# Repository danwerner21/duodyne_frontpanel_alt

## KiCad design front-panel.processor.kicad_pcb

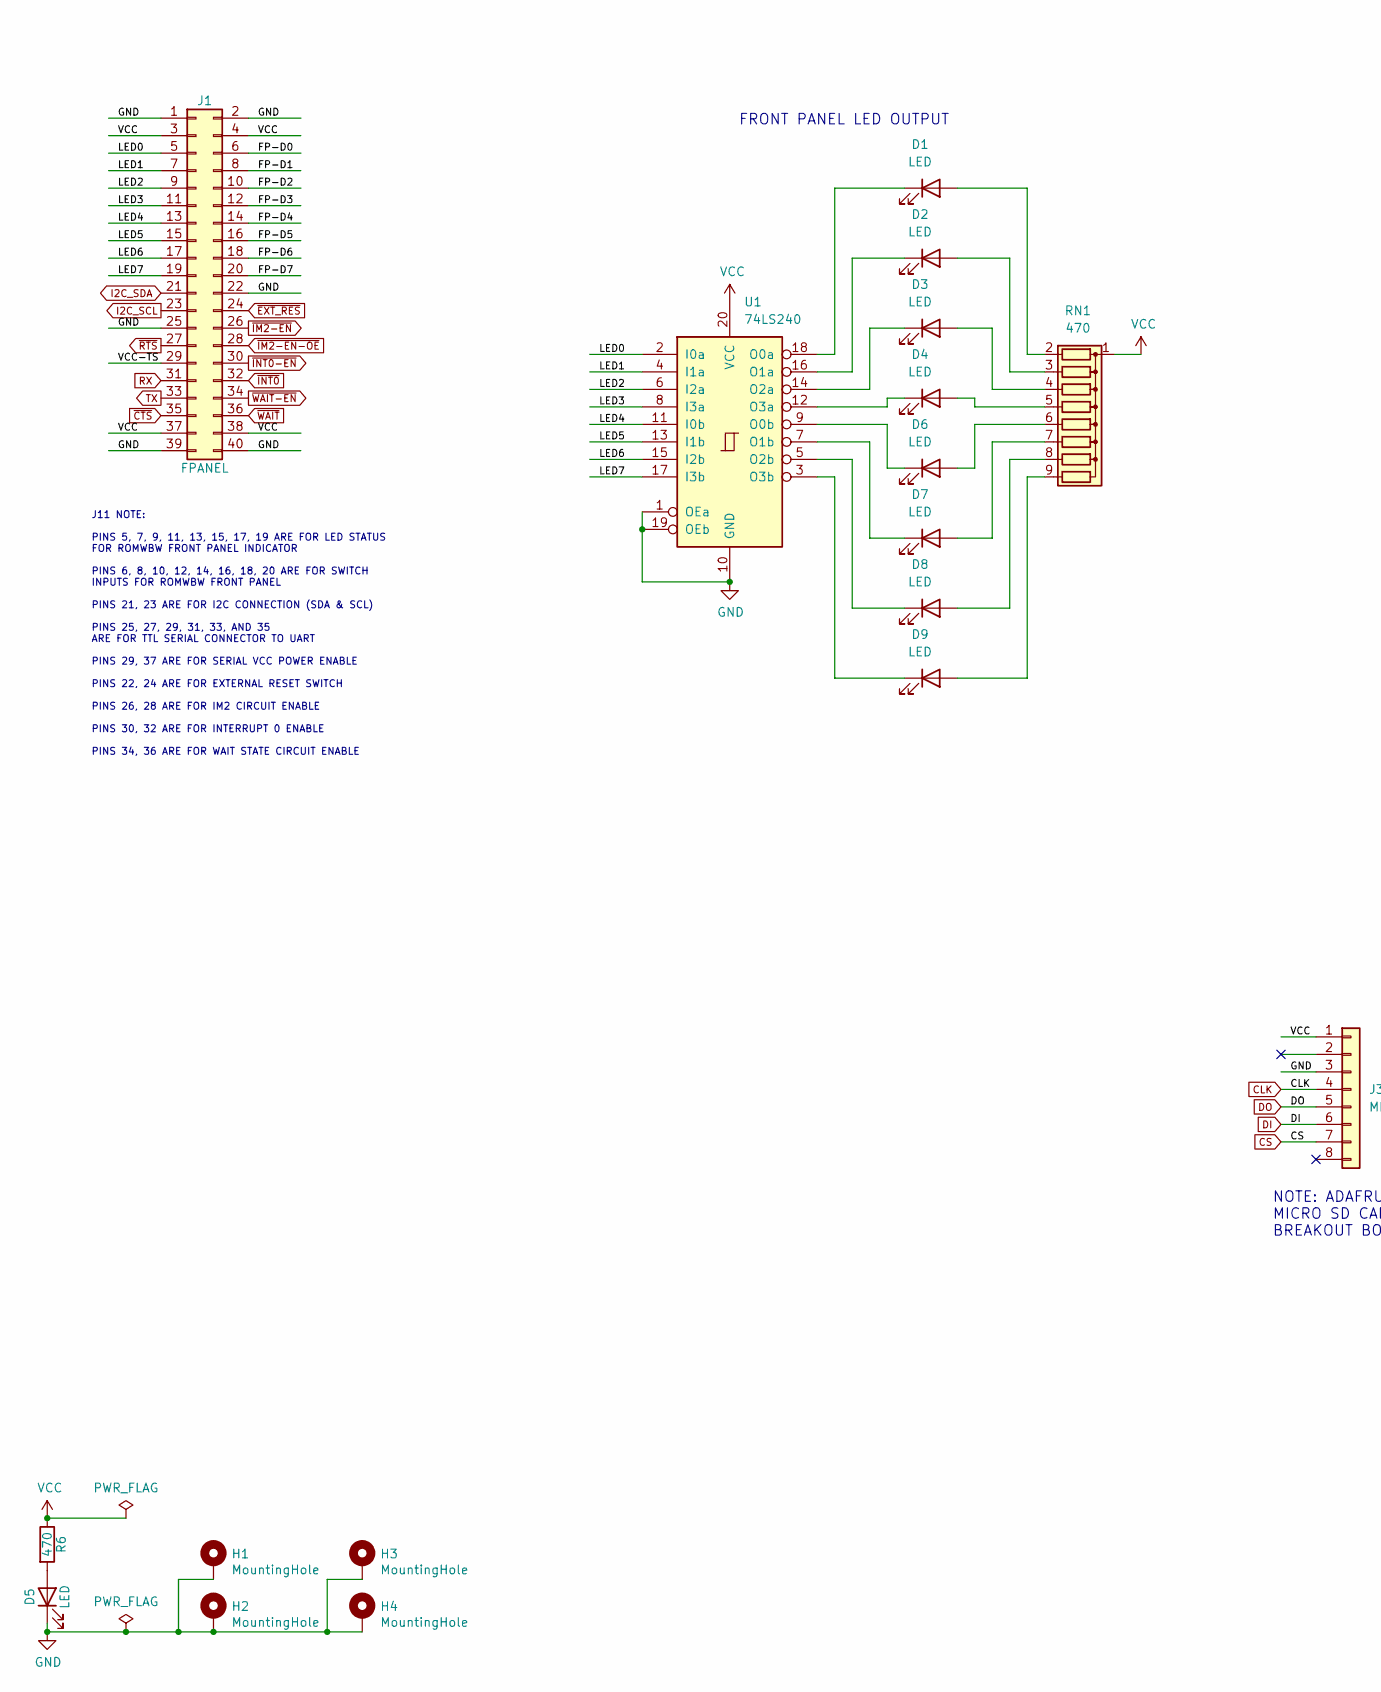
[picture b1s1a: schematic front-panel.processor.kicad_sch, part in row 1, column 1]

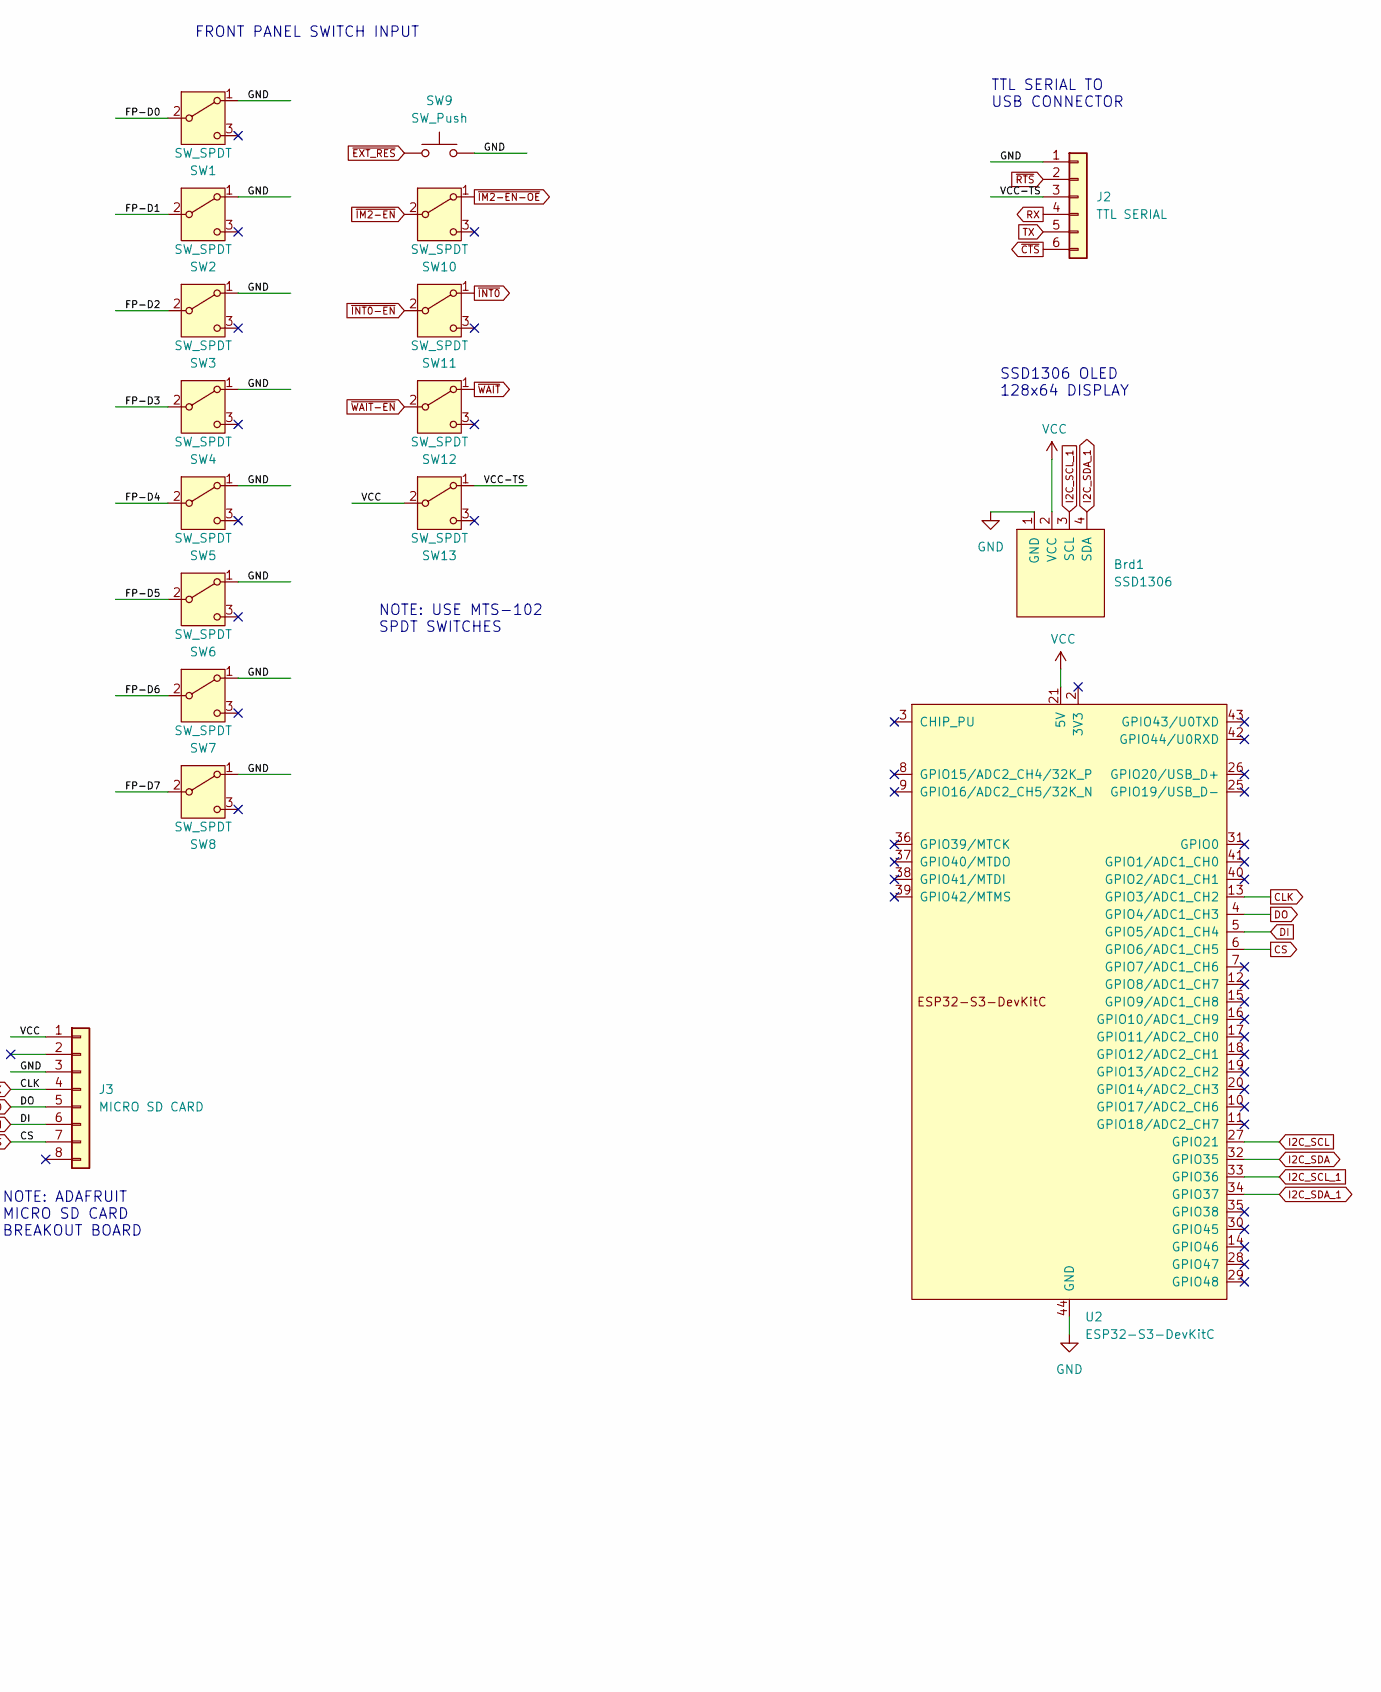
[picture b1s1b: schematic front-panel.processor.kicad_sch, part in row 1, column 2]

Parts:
Brd1: SSD1306; 128x64OLED
D1, D2, D3, D4, D5, D6, D7, D8, D9: LED; LED_D3.0mm
H1, H2, H3, H4: MountingHole; MountingHole_3.2mm_M3_Pad
J1: FPANEL; IDC-Header_2x20_P2.54mm_Horizontal
J2: TTL SERIAL; PinHeader_1x06_P2.54mm_Vertical
J3: MICRO SD CARD; PinSocket_1x08_P2.54mm_Vertical
R6: 470; R_Axial_DIN0207_L6.3mm_D2.5mm_P7.62mm_Horizontal
RN1: 470; R_Array_SIP9
SW1, SW2, SW3, SW4, SW5, SW6, SW7, SW8, SW10, SW11, SW12, SW13: SW_SPDT; SW_Toggle_Blue_wSlots
SW9: SW_Push; SW_PUSH_6mm
U1: 74LS240; DIP-20_W7.62mm
U2: ESP32-S3-DevKitC

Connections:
/FP-D0: J1.6, SW1.2 (B)
/FP-D1: J1.8, SW2.2 (B)
/FP-D2: J1.10, SW3.2 (B)
/FP-D3: J1.12, SW4.2 (B)
/FP-D4: J1.14, SW5.2 (B)
/FP-D5: J1.16, SW6.2 (B)
/FP-D6: J1.18, SW7.2 (B)
/FP-D7: J1.20, SW8.2 (B)
/LED0: J1.5, U1.2 (I0a)
/LED1: J1.7, U1.4 (I1a)
/LED2: J1.9, U1.6 (I2a)
/LED3: J1.11, U1.8 (I3a)
/LED4: J1.13, U1.11 (I0b)
/LED5: J1.15, U1.13 (I1b)
/LED6: J1.17, U1.15 (I2b)
/LED7: J1.19, U1.17 (I3b)
/VCC-TS: J1.29, J2.3, SW13.1 (A)
CLK: J3.4, U2.13 (GPIO3/ADC1_CH2)
CS: J3.7, U2.6 (GPIO6/ADC1_CH5)
DI: J3.6, U2.5 (GPIO5/ADC1_CH4)
DO: J3.5, U2.4 (GPIO4/ADC1_CH3)
GND: Brd1.1 (GND), D5.1 (K), H1.1, H2.1, H3.1, H4.1, J1.1, J1.2, J1.22, J1.25, J1.39, J1.40, J2.1, J3.3, SW1.1 (A), SW2.1 (A), SW3.1 (A), SW4.1 (A), SW5.1 (A), SW6.1 (A), SW7.1 (A), SW8.1 (A), SW9.2, U1.1 (OEa), U1.10 (GND), U1.19 (OEb), U2.22 (GND), U2.23 (GND), U2.24 (GND), U2.44 (GND)
I2C_SCL: J1.23, U2.27 (GPIO21)
I2C_SCL_1: Brd1.3 (SCL), U2.33 (GPIO36)
I2C_SDA: J1.21, U2.32 (GPIO35)
I2C_SDA_1: Brd1.4 (SDA), U2.34 (GPIO37)
unnamed: D1.2 (A), RN1.2 (R1)
unnamed: D1.1 (K), U1.18 (O0a)
unnamed: D2.2 (A), RN1.3 (R2)
unnamed: D2.1 (K), U1.16 (O1a)
unnamed: D3.2 (A), RN1.4 (R3)
unnamed: D3.1 (K), U1.14 (O2a)
unnamed: D4.2 (A), RN1.5 (R4)
unnamed: D4.1 (K), U1.12 (O3a)
unnamed: D5.2 (A), R6.2
unnamed: D6.2 (A), RN1.6 (R5)
unnamed: D6.1 (K), U1.9 (O0b)
unnamed: D7.2 (A), RN1.7 (R6)
unnamed: D7.1 (K), U1.7 (O1b)
unnamed: D8.2 (A), RN1.8 (R7)
unnamed: D8.1 (K), U1.5 (O2b)
unnamed: D9.2 (A), RN1.9 (R8)
unnamed: D9.1 (K), U1.3 (O3b)
RX: J1.31, J2.4
TX: J1.33, J2.5
VCC: Brd1.2 (VCC), J1.3, J1.4, J1.37, J1.38, J3.1, R6.1, RN1.1 (common), SW13.2 (B), U1.20 (VCC), U2.21 (5V)
~CTS: J1.35, J2.6
~EXT_RES: J1.24, SW9.1
~IM2-EN-OE: J1.28, SW10.1 (A)
~IM2-EN: J1.26, SW10.2 (B)
~INT0-EN: J1.30, SW11.2 (B)
~INT0: J1.32, SW11.1 (A)
~RTS: J1.27, J2.2
~WAIT-EN: J1.34, SW12.2 (B)
~WAIT: J1.36, SW12.1 (A)

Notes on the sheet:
SSD1306 OLED 128x64 DISPLAY
FRONT PANEL LED OUTPUT
J11 NOTE: PINS 5, 7, 9, 11, 13, 15, 17, 19 ARE FOR LED STATUS FOR ROMWBW FRONT PANEL INDICATOR PINS 6, 8, 10, 12, 14, 16, 18, 20 ARE FOR SWITCH INPUTS FOR ROMWBW FRONT PANEL PINS 21, 23 ARE FOR I2C CONNECTION (SDA & SCL) PINS 25, 27, 29, 31, 33, AND 35 ARE FOR TTL SERIAL CONNECTOR TO UART PINS 29, 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
NOTE: ADAFRUIT MICRO SD CARD BREAKOUT BOARD
NOTE: USE MTS-102 SPDT SWITCHES
FRONT PANEL SWITCH INPUT
TTL SERIAL TO USB CONNECTOR

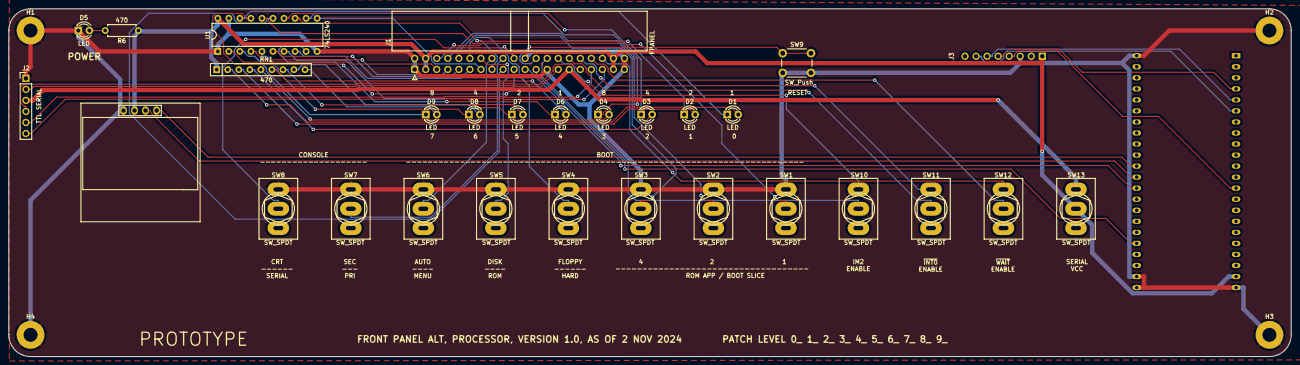
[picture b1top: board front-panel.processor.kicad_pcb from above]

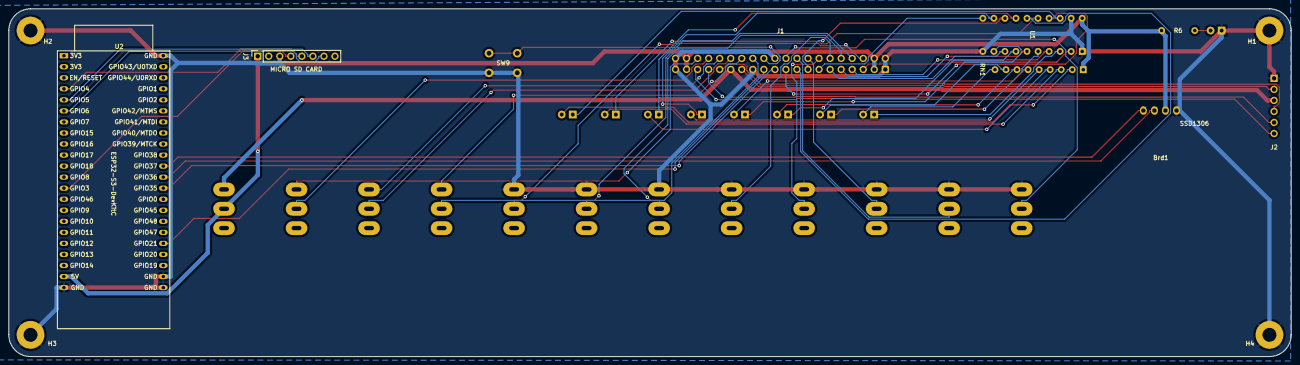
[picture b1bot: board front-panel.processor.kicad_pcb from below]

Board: 2 copper layers, 295.0 x 80.0 mm, 34 parts (2 on the bottom side), 55 nets.

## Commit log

2024-11-02 initial
